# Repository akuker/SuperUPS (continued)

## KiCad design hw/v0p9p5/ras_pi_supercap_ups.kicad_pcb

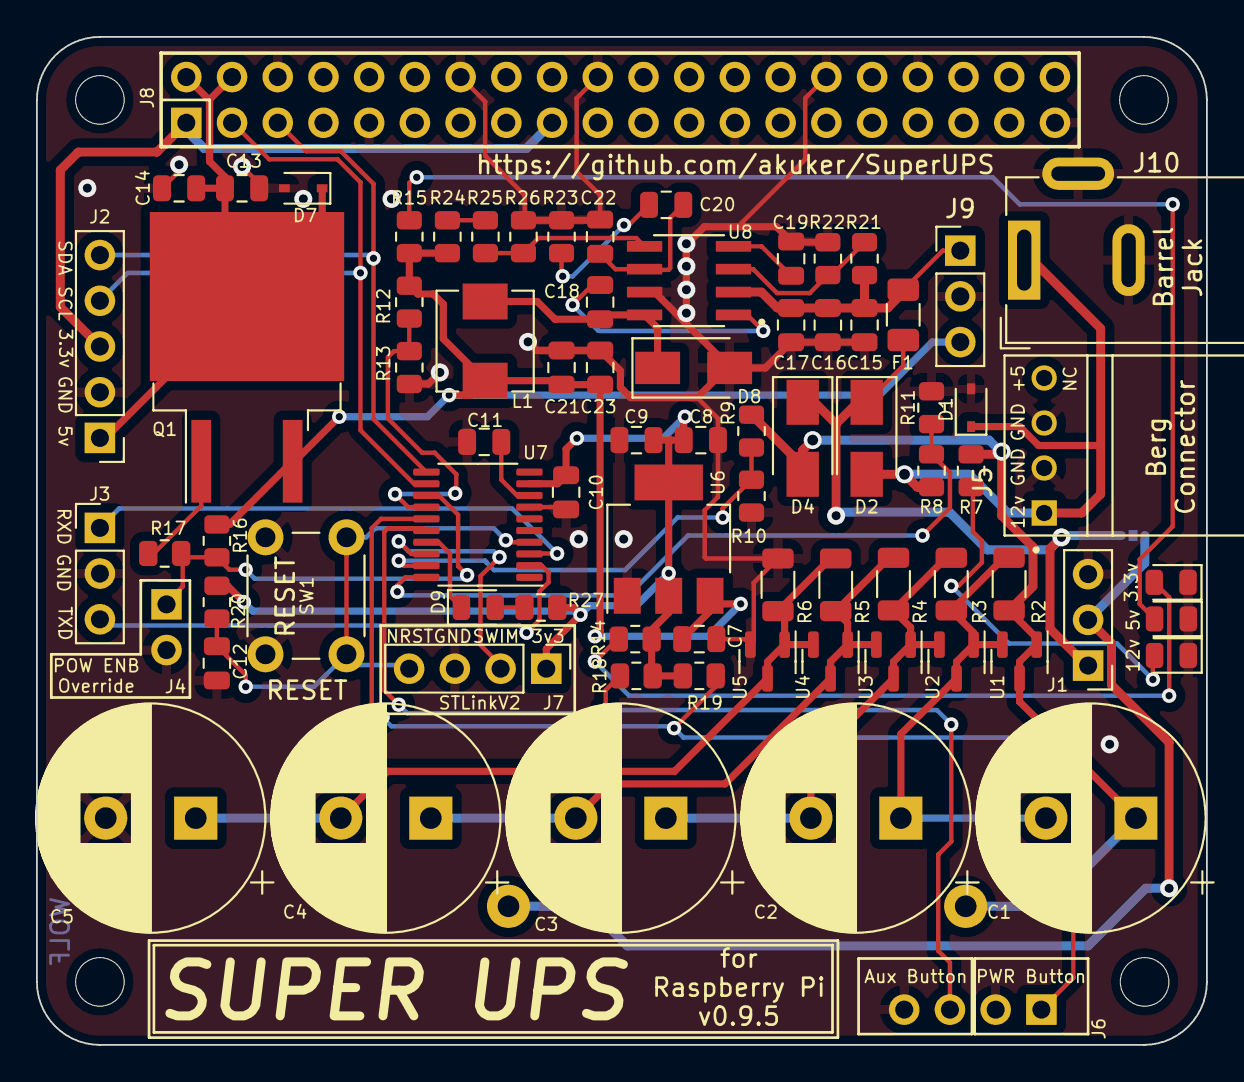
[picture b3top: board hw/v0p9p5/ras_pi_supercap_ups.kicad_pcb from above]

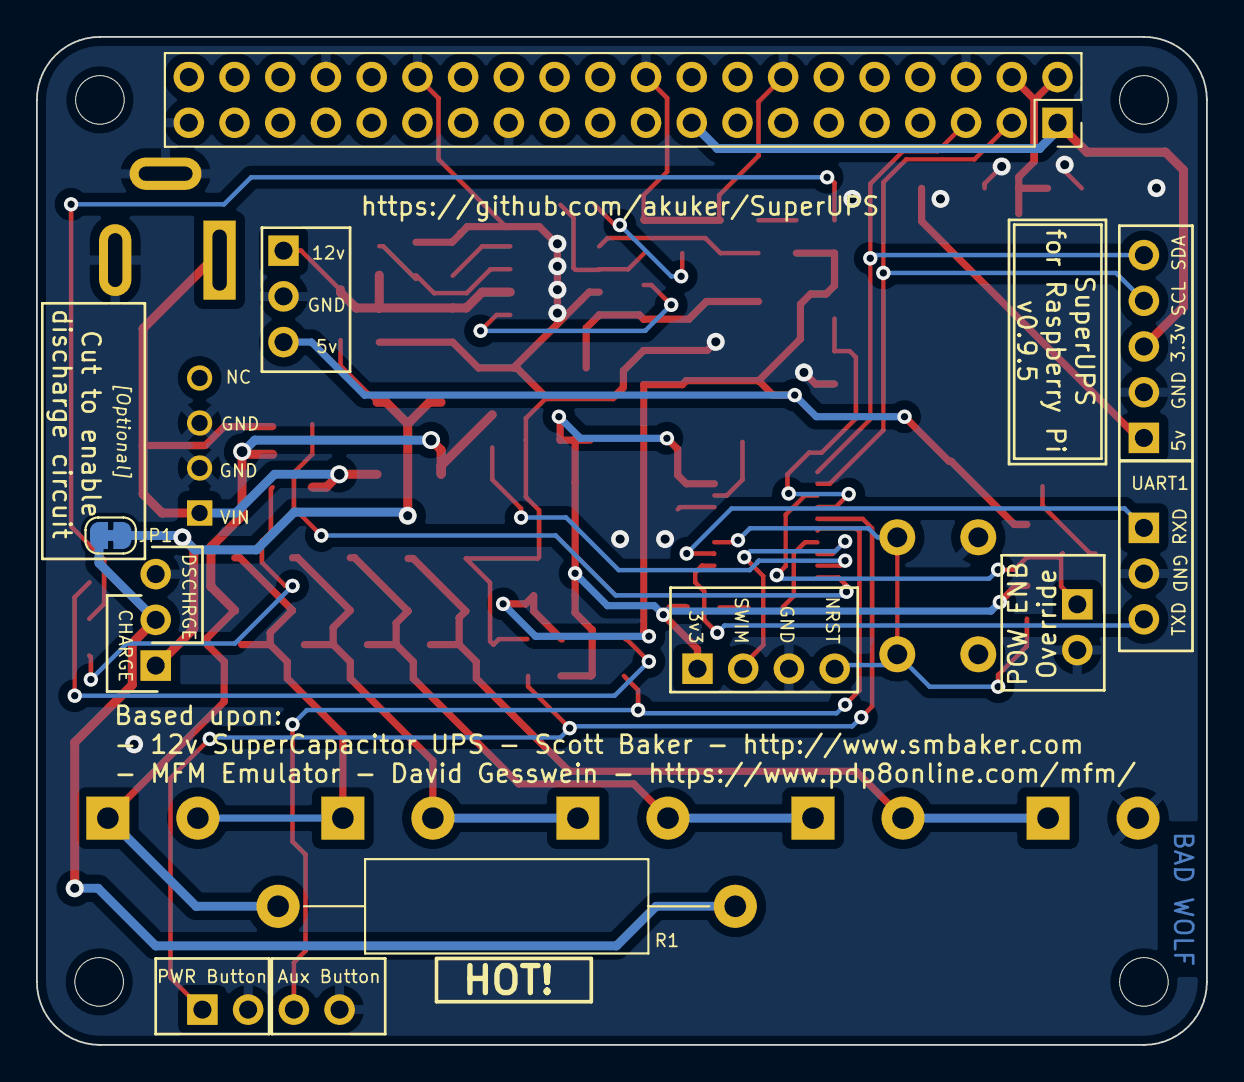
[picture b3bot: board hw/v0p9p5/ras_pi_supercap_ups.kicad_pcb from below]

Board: 2 copper layers, 65.0 x 56.0 mm, 85 parts (3 on the bottom side), 41 nets.

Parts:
C1, C2, C3, C4, C5: 10F; CP_Radial_D12.5mm_P5.00mm
C7, C8, C10, C13: 10u; C_0805_2012Metric
C9, C14, C18: 100n; C_0805_2012Metric
C11, C12: 1u; C_0805_2012Metric
C15, C16: 4.7u; C_0805_2012Metric
C17, C20: 4.7n; C_0805_2012Metric
C19: 10n; C_0805_2012Metric
C21, C23: 33u; C_0805_2012Metric
C22: 39p; C_0805_2012Metric
D1, D7: PTVSHC3D15VUH; D_SOD-323
D2, D4: B340LA-13-F; D_SMA
D3, D5, D6, D9: Green; LED_0805_2012Metric
D8: B340A; D_SMA
F1: Fuse_Small; Fuse_1206_3216Metric
H1, H2, H3, H4: MountingHole; MountingHole_2.7mm_M2.5
J1, J3: Conn_01x03; PinHeader_1x03_P2.54mm_Vertical
J2: Conn_01x05; PinHeader_1x05_P2.54mm_Vertical
J4: Force Power On; PinHeader_1x02_P2.54mm_Vertical
J5: 171826-4; TE_171826-4
J6: LEDs and Buttons; PinHeader_1x04_P2.54mm_Vertical
J7: STLinkV2 Connector; PinHeader_1x04_P2.54mm_Vertical
J8: Raspberry_Pi_2_3; PinSocket_2x20_P2.54mm_Vertical
J9: Test Points; PinHeader_1x03_P2.54mm_Vertical
J10: Barrel_Jack; BarrelJack_Wuerth_6941xx301002
JP1: Charge Enb; SolderJumper-2_P1.3mm_Bridged_RoundedPad1.0x1.5mm
L1: 6.8uH; Sunltech_SLO0530H
Q1: IRF5305; TO-263-2
R1: 10 3W; R_Axial_DIN0516_L15.5mm_D5.0mm_P25.40mm_Horizontal
R2, R3, R4, R5, R6: 1k; R_1206_3216Metric
R7, R14, R15, R17, R18, R19, R27: 1k; R_0805_2012Metric
R8, R9, R12, R16, R20: 10k; R_0805_2012Metric
R10, R11, R13: 2.2k; R_0805_2012Metric
R21: 332k; R_0805_2012Metric
R22: 68.1k; R_0805_2012Metric
R23: 49.9k; R_0805_2012Metric
R24: 0; R_0805_2012Metric
R25: 10.2k; R_0805_2012Metric
R26: 2k; R_0805_2012Metric
SW1: Reset; SW_PUSH_6mm_H4.3mm
U1, U2, U3, U4, U5: KA431SMFTF; SOT-23
U6: AMS1117-3.3; SOT-223-3_TabPin2
U7: STM8S003F3P; TSSOP-20_4.4x6.5mm_P0.65mm
U8: TPS54331DR; SOIC127P599X175-8N

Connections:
+3V3: C8.1, C9.1, C10.1, J7.1, R14.1, R18.1, R19.1, R20.2, R27.1, U6.2 (VO), U7.9 (VDD)
+5V: C7.1, C21.1, C23.1, J9.3, L1.2, Q1.3 (S), R12.1, R15.1, R16.1, R24.1, U6.3 (VI)
+12V: C15.1, C16.1, C17.1, F1.2, J9.1, R21.1, U8.2 (VIN)
DEBUG_LED: D9.1 (K), U7.17 (PC7)
GND: C5.2, C7.2, C8.2, C9.2, C10.2, C11.2, C12.2, C13.2, C14.2, C15.2, C16.2, C17.2, C19.2, C21.2, C22.2, C23.2, D1.2 (A2), D3.1 (K), D5.1 (K), D6.1 (K), D7.2 (A2), D8.2 (A), J1.3, J2.2, J3.2, J4.2, J5.2, J5.3, J6.2, J6.4, J7.3, J8.6 (GND), J8.9 (GND), J8.14 (GND), J8.20 (GND), J8.25 (GND), J8.30 (GND), J8.34 (GND), J8.39 (GND), J9.2, J10.2, J10.3, R6.2, R10.2, R11.1, R13.2, R22.2, R23.2, R26.2, SW1.1, U5.2 (K), U6.1 (GND), U7.7 (VSS), U8.7 (GND)
I2C_SCL: J2.4, J8.3 (SDA/GPIO2), U7.12 (PB4)
I2C_SDA: J2.5, J8.5 (SCL/GPIO3), U7.11 (PB5)
NRST: C12.1, J7.4, R20.1, SW1.2, U7.4 (NRST)
unnamed: C1.1, D4.2 (A), R1.2, R2.1, R7.1, R9.1, U1.1 (REF), U1.3 (A)
unnamed: C1.2, C2.1, R2.2, R3.1, U1.2 (K), U2.1 (REF), U2.3 (A)
unnamed: C2.2, C3.1, R3.2, R4.1, U2.2 (K), U3.1 (REF), U3.3 (A)
unnamed: C3.2, C4.1, R4.2, R5.1, U3.2 (K), U4.1 (REF), U4.3 (A)
unnamed: C4.2, C5.1, R5.2, R6.1, U4.2 (K), U5.1 (REF), U5.3 (A)
unnamed: C11.1, U7.8 (VCAP)
unnamed: C18.1, D8.1 (K), L1.1, U8.8 (PH)
unnamed: C18.2, U8.1 (BOOT)
unnamed: C19.1, U8.4 (SS)
unnamed: C20.1, C22.1, U8.6 (COMP)
unnamed: C20.2, R23.1
unnamed: D2.1 (K), D4.1 (K), F1.1, J1.1, JP1.2 (B)
unnamed: D3.2 (A), R7.2
unnamed: D5.2 (A), R14.2
unnamed: D6.2 (A), R15.2
unnamed: D9.2 (A), R27.2
unnamed: J1.2, JP1.1 (A), R1.1
unnamed: Q1.1 (G), R17.2
unnamed: R21.2, R22.1, U8.3 (EN)
unnamed: R24.2, R25.1
unnamed: R25.2, R26.1, U8.5 (VSENSE)
PI_3v3: J2.3, J8.1 (3V3), J8.17 (3V3)
POW_ENABLE: J4.1, R16.2, R17.1, U7.13 (PC3)
POW_OUT: C13.1, C14.1, D7.1 (A1), J2.1, J8.2 (5V), J8.4 (5V), Q1.2 (D)
Power_Button: J6.1, R19.2, U7.15 (PC5)
RS232_RXD: J3.1, U7.3 (PD6)
RS232_TXD: J3.3, U7.2 (PD5)
SWIM: J7.2, U7.18 (PD1)
Spare_Button: J6.3, R18.2, U7.16 (PC6)
UPS_SENSE: R9.2, R10.1, U7.19 (PD2)
VIN: D1.1 (A1), D2.2 (A), J5.1, J10.1, R8.1
VIN_SENSE: R8.2, R11.2, U7.20 (PD3)
VOUT_SENSE: R12.2, R13.1, U7.14 (PC4)

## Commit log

2022-05-19 Reorganized directories
2022-05-19 Changing to BSD 3 clause license, with permission from Scott Baker
2022-05-19 Set theme jekyll-theme-hacker
2022-05-19 Move akuker supercap board from github.com/akuker/hw_projects
2022-05-19 Add gitignore
2022-05-19 Add docs
2022-05-19 add native version of draw.io diagrams
2022-05-19 pictures of the board
2022-05-19 Logo from PotatoFi
2022-05-24 Baseline version of S.M.Baker's code for ATTiny85
2022-05-24 Demo project to blink the led
2022-05-31 example CMakeLists from https://github.com/ulikoehler/stm8s-discovery-sdcc-blink
2022-05-31 working uart with SPL
2022-05-31 ignore temp files
2022-05-31 add SPL reference
2022-05-31 fix file extension
2022-05-31 blinky and uart working
2022-05-31 AIN3 and 4 working
2022-05-31 i2cdetect runs VERY slow
2022-05-31 i2c detection works!
2022-05-31 i2cset and i2cget working
2022-05-31 read real adc data
2022-05-31 rename main.c
2022-05-31 enabled printf
2022-06-01 demo I2c program
2022-06-01 Formatting cleanup
2022-06-01 restructured directories
2022-06-01 Added vout sense
2022-06-01 baseline
2022-06-02 updates... pulled in buck conv
2022-06-02 Updates - candidate board layout
2022-06-18 Integrated with v9.5 board. Enabled state machine
2022-06-20 Added libcrc
2022-06-20 integration updates and cleanup
2022-06-20 Add external crc repo
2022-06-20 Added timer-based delay functions
2022-06-20 remove commented-out code
2022-06-20 cleanup
2022-06-20 github wants carriage returns at the end of the file
2022-06-20 adjust main loop timer and adjust debug rs-232 output
2022-06-22 re-write of UPS controller interface class
2022-06-22 tests for the ups class
2022-06-22 tests for getters and setters
2022-06-24 Address warnings from splint
2022-06-24 Add gpio handler and device id
2022-06-24 remove extraneous file
2022-06-24 Integrated shutdown/aux button reading
2022-06-26 initial commit v1p0
2022-06-29 Added note about R26
2022-07-02 Last version before removing mosfet
2022-07-02 Ignore Mac junk file
2022-07-02 add missing file
2022-07-02 Removed Mosfet - release candidate 1.0
2022-07-02 Change power control resistor to jumper
2022-07-05 As-Ordered version
2022-07-15 added ring buffer
2022-07-15 working updates
2022-07-15 Add option to send STDOUT over the i2c bus
2022-07-19 Added register to control debug LED
2022-07-19 moved daemon to separate file. Added raw/voltage conversions
2022-07-20 Pogo pin holder
2022-07-22 added logic to poll the controller's console output
2022-08-07 Remove debug output. Print state transitions and build date only
2022-08-07 archive test for the ring buffer. Replace main.c with this file
2022-08-07 fix delay after power loss to hold up Pi for max 5 seconds
2022-08-08 change i2c clock to 1Mhz for better compatibility
2022-08-08 integration updates
2022-09-07 Cleanup files
2022-09-08 New ups.service file for daemonization, updated SETUP.md with updated commands to setup automated start on boot.
2022-09-08 Updated script/service names
    Updated to place python scripts in /usr/local/bin instead
    Renamed ups.service to superups.service, also updated to /usr/local/bin/
    Renamed upsdaemon.py to superupsdaemon.py
    Removed disclaimer in SETUP.md about being incomplete
2022-09-08 first draft
2022-09-08 get rid of macos temp file
2022-10-24 Corrected SETUP.md and service file to properly reflect superupsdaemon.py script
2023-04-10 new v1.1 - added schotky diode
2023-04-11 fix D1 and D7 part number
